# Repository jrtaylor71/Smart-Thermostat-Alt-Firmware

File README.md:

# Smart Thermostat Alt Firmware

A comprehensive, feature-rich smart thermostat system built on the ESP32 platform with professional PCB design. Perfect for DIY smart home automation with full Home Assistant integration.

## 🏗️ Hardware Credits

This project is **alternative firmware** for the excellent smart-thermostat hardware designed by **Stefan Meisner**.

**Original Hardware Project**: https://github.com/smeisner/smart-thermostat

We use Stefan's hardware design and provide an enhanced firmware implementation with advanced features including multi-core architecture, centralized display management, and comprehensive Home Assistant integration.

## 🌟 Key Features

- **📱 Local Touch Control**: ILI9341 TFT LCD with intuitive touch interface
- **🏠 Smart Home Ready**: Full MQTT integration with Home Assistant auto-discovery
- **🔄 Bidirectional Schedule Sync (v1.4.001)**: 7-day schedules stay in sync between thermostat and Home Assistant (device ↔ HA) with day/night periods and editable Heat/Cool/Auto temperatures
- **📅 7-Day Scheduling**: Comprehensive inline scheduling with day/night periods and editable Heat/Cool/Auto temperatures
- **🌡️ Dual Sensors**: AHT20 for ambient conditions + DS18B20 for hydronic systems
- **⚡ Multi-Stage HVAC**: Support for 2-stage heating and cooling systems
- **💨 Advanced Fan Control**: Auto, continuous, and scheduled cycling modes
- **🌤️ Weather Integration**: OpenWeatherMap and Home Assistant weather with color-coded icons on display
- **🌐 Modern Web Interface**: Complete tabbed interface with embedded scheduling - no separate pages
- **📡 Offline Operation**: Full functionality without WiFi connection
- **🔧 Professional PCB**: Custom PCB design for clean, permanent installation
- **🔄 OTA Updates**: Over-the-air firmware updates with real-time progress tracking
- **🔒 Factory Reset**: Built-in reset capability via boot button

## 🚀 Quick Start

### Hardware Requirements
- ESP32-S3-WROOM-1-N16 (16MB Flash, No PSRAM) 
- ILI9341 320x240 TFT LCD with XPT2046 Touch Controller
- AHT20 Temperature/Humidity Sensor (I2C)
- DS18B20 Temperature Sensor (optional, for hydronic heating)
- LD2410 24GHz mmWave Motion Sensor (optional, for display wake)
- 5x Relay Module for HVAC control
- Custom PCB by Stefan Meisner (files included)

### Software Setup
1. Install [PlatformIO](https://platformio.org/) IDE
2. Clone this repository
3. Open project in PlatformIO
4. Configuration optimized for ESP32-S3-WROOM-1-N16 (16MB flash)
5. Memory usage: RAM 15.2% (49728/327680 bytes); Flash 18.5% (1209901/6553600 bytes, default_16mb.csv partition)
6. Erase flash if you are using firmware from Stefan Meisner (original firmware).
7. Build and upload to ESP32-S3
8. Use touch interface to configure WiFi and settings

## 💻 Web Interface

Access the thermostat's web interface by navigating to its IP address:

### Tabbed Interface with Embedded Features

**Status Tab**: Real-time monitoring of:
- Current temperature and humidity
- Thermostat and fan modes
- Relay states and system status

**Settings Tab**: Complete configuration interface for:

- Temperature setpoints and control modes
- MQTT/Home Assistant integration
- WiFi network settings
- Multi-stage HVAC parameters
- Hydronic heating controls
- Fan scheduling options

**Schedule Tab**: Comprehensive 7-day scheduling:
- Day and night periods for each day of the week
- Editable Heat, Cool, and Auto temperatures for each period
- Time controls for period transitions
- Schedule enable/disable and override controls
- All options always visible - no hidden menus

**System Tab**: Device information and firmware updates

## 🏠 Home Assistant Integration

Automatic discovery and integration with Home Assistant:

1. Enable MQTT in thermostat settings
2. Configure MQTT broker details
3. Thermostat appears automatically in Home Assistant
4. Full control via Home Assistant interface (climate entity, helpers, and switches)
5. Bidirectional schedule sync: HA helpers (77 per thermostat) mirror the device schedule; edits on either side stay in sync
6. Supports climate entity with heating/cooling modes

## 🛠️ Advanced Features

### Multi-Stage Operation
- Intelligent staging based on time and temperature
- Configurable stage 2 activation parameters
- Prevents system short-cycling
- Optimizes energy efficiency

### Hydronic Heating Support
- DS18B20 water temperature monitoring
- Safety interlocks prevent operation when water is too cold
- Configurable high/low temperature thresholds
- Perfect for radiant floor heating systems

### Fan Control Options
- **Auto**: Fan runs only with heating/cooling
- **On**: Continuous fan operation
- **Cycle**: Scheduled fan operation (configurable minutes per hour)

### Motion Detection
- **LD2410 24GHz mmWave Sensor**: Automatic display wake on motion detection
- **Hardware Pins**: RX=15, TX=16, Motion=18
- **Robust Detection**: Works with sensors that don't respond to UART commands
- **Home Assistant Integration**: Motion sensor auto-discovery and status publishing
- **Energy Saving**: Display automatically sleeps when no motion detected
- **Seamless Operation**: Works alongside existing touch controls

### Safety Features
- Watchdog timer prevents system lockups
- Factory reset via boot button (10+ seconds)
- Temperature limit enforcement
- Graceful offline operation

## 🔧 Factory Reset

Press and hold the boot button for more than 10 seconds while the thermostat is running to restore all settings to defaults.

## 📄 License

This project is released under the GNU General Public License v3.0. Free to use, modify, and distribute.

## 🤝 Contributing

Contributions welcome! Please:
1. Fork the repository
2. Create a feature branch
3. Make your changes
4. Submit a pull request

## 📞 Support

- **Issues**: Use GitHub Issues for bug reports
- **Discussions**: GitHub Discussions for questions
- **Documentation**: Comprehensive docs included
- **Serial Debug**: Detailed logging at 115200 baud

## ⭐ Version

**Current Version**: 1.4.001 (January 2026)
### Release Notes: 1.4.001
- Bidirectional MQTT schedule synchronization (thermostat ↔ Home Assistant)
- Fixed day index off-by-one bug (MQTT Monday=0, firmware Sunday=0)
- Multi-thermostat support with centralized inbound automation and 77 outbound automations per device
- 77 Home Assistant helpers per thermostat (14 times, 42 temps, 21 booleans)
- Added automation generator and schedule templates for HA
- Updated documentation and quick-start guidance for schedule sync

### Previous Highlights (1.3.8)
- Weather Integration: Dual-source weather support (OpenWeatherMap and Home Assistant)
- Weather Display: Color-coded standard OWM icons with temperature, conditions, and high/low display
- Weather Web Interface: Dedicated weather tab with AJAX form submission
- Anti-Flicker Display: Cached redraw optimization for time and weather elements
- Enhanced Time Display: Improved format "HH:MM Weekday Mon D YYYY" with flicker elimination
- Weather Settings: Configurable update intervals (5-60 minutes) with state field for US cities
- Enhanced OTA Updates: Real-time progress tracking for upload and flash write operations
- Improved OTA UX: Integrated OTA interface in System tab with status messages and reboot timing
- 7-Day Scheduling System: Complete inline scheduling with day/night periods and editable Heat/Cool/Auto temperatures
- LD2410 Motion Sensor Integration: 24GHz mmWave radar for automatic display wake with robust detection
- Modern Tabbed Web Interface: All features embedded in main page - Status, Settings, Schedule, Weather, and System tabs
- Enhanced MQTT Integration: Motion sensor auto-discovery and status publishing to Home Assistant
- ESP32-S3-WROOM-1-N16 platform with 16MB flash optimization
- Modern Material Design color scheme with enhanced readability
- Complete thermostat functionality with Option C display system
- Enhanced MQTT/Home Assistant integration with temperature precision
- Professional PCB design (hardware by Stefan Meisner)
- Multi-stage HVAC support with intelligent staging
- Dual-core FreeRTOS architecture for ESP32-S3

## 🙏 Credits & Acknowledgments

**Hardware Design**: Stefan Meisner - [smart-thermostat](https://github.com/smeisner/smart-thermostat)  
**Alternative Firmware**: Jonn Taylor - Enhanced firmware implementation

This project demonstrates the power of open-source collaboration - combining excellent hardware design with advanced firmware capabilities.

---

**Created for the DIY smart home community**

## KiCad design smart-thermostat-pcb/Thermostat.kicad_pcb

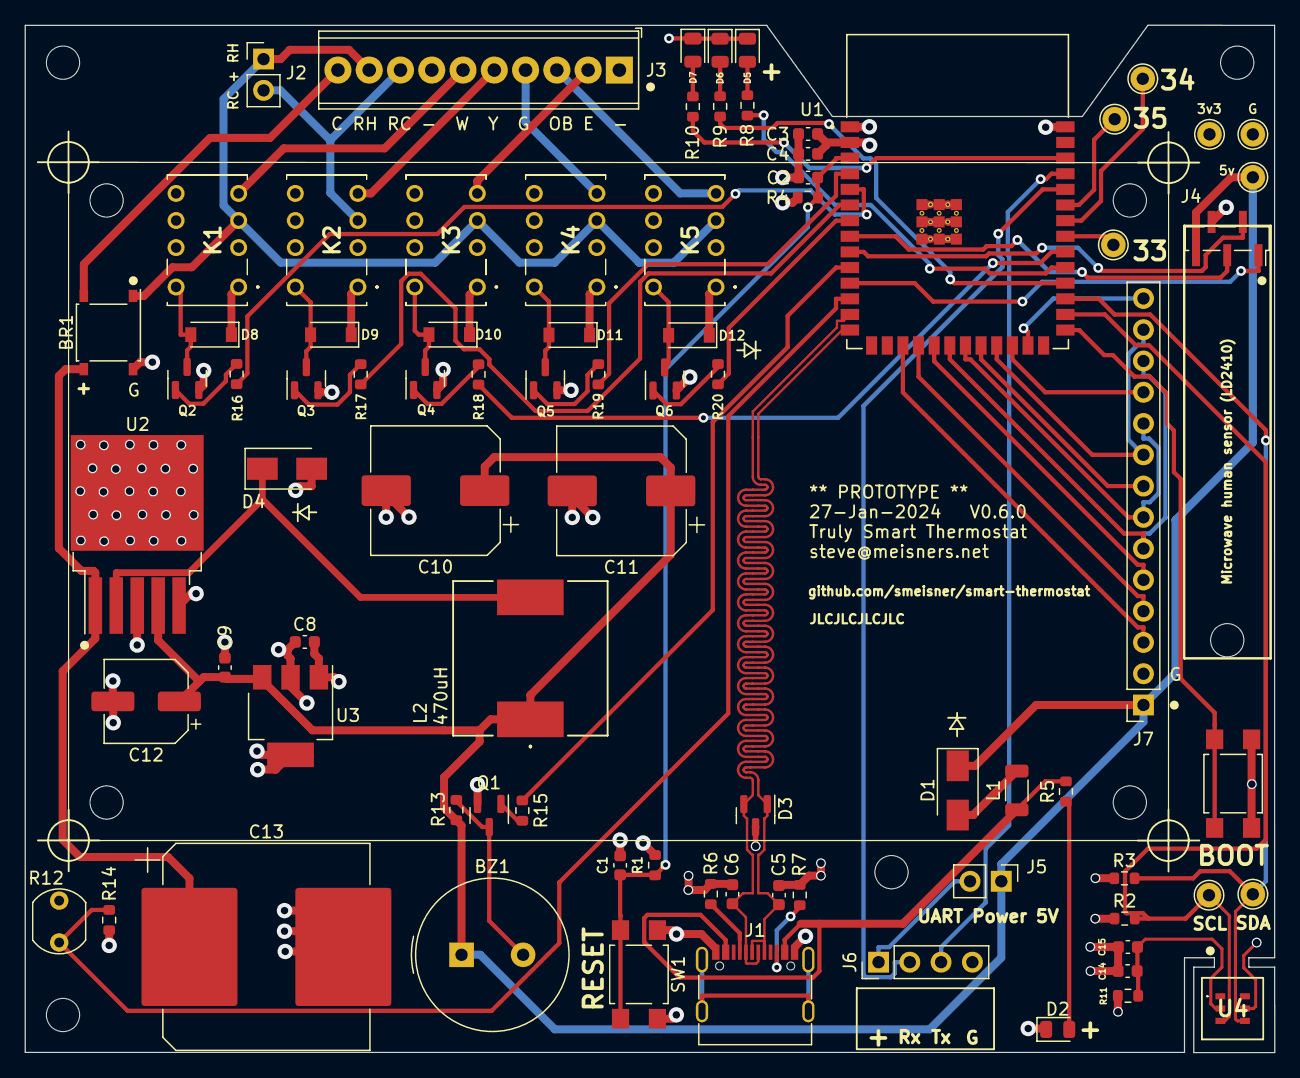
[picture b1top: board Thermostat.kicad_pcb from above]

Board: 4 copper layers, 101.5 x 83.4 mm, 91 parts (0 on the bottom side), 65 nets.

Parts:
BR1: MB6S; Diode_Bridge_Diotec_ABS
BZ1: Buzzer; Buzzer_TDK_PS1240P02BT_D12.2mm_H6.5mm
C1, C2: 1uF; C_0603_1608Metric
C3, C14: 0.1uF; C_0603_1608Metric
C4: 22uF; C_0603_1608Metric
C5, C6: 22pF; C_0603_1608Metric
C8, C9, C15: 10uF; C_0603_1608Metric
C10, C11: 470uF; CP_Elec_10x10
C12: 47uF; CP_Elec_6.3x7.7
C13: 680uF; CP_Elec_16x17.5
D1: D_Zener; D_SMA
D2, D5, D6, D7: LED; LED_0805_2012Metric
D3: SP0502BAHT; SOT-23
D4: SS34; D_SMA
D8, D9, D10, D11, D12: 1N4148W; D_SOD-123
H1, H2, H3, H4, H5, H6, H7, H8, H9: MountingHole; MountingHole_2.7mm_M2.5
J1: USB_C_Receptacle_USB2.0; USB_C_Receptacle_G-Switch_GT-USB-7010ASV
J2: RC+RH; PinHeader_1x02_P2.54mm_Vertical
J3: Screw_Terminal_01x10; TerminalBlock_Phoenix_MPT-0,5-10-2.54_1x10_P2.54mm_Horizont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
J4: LD2410; PinSocket_1x05_P1.27mm_Vertical_SMD_Pin1Right
J5: UART PWR; PinHeader_1x02_P2.54mm_Vertical
J6: Conn_01x04; PinHeader_1x04_P2.54mm_Vertical
J7: MSP3218; PinSocket_1x14_P2.54mm_Vertical
K1, K2, K3, K4, K5: UC2-3NJ; UC23NJ
L1: 600ohm; L_1206_3216Metric
L2: 470uH; IND_CDRH127_LDNP-470MC_SUM
Q1, Q2, Q3, Q4, Q5, Q6: 2N7002; SOT-23
R1, R2, R3, R4, R13, R14: 10k; R_0603_1608Metric
R5: 10K; R_0603_1608Metric
R6, R7: 5.1K; R_0603_1608Metric
R8, R10: 1K; R_0603_1608Metric
R9: 2K; R_0603_1608Metric
R11: 220; R_0603_1608Metric
R12: LDR07; R_LDR_5.1x4.3mm_P3.4mm_Vertical
R15: 1k; R_0603_1608Metric
R16, R17, R18, R19, R20: 470; R_0603_1608Metric
SW1: Reset; SW_SPST_TL3305A
SW2: Boot; SW_SPST_TL3305A
TP1: SCL; TestPoint_THTPad_D2.0mm_Drill1.0mm
TP2: SDA; TestPoint_THTPad_D2.0mm_Drill1.0mm
TP3: 3v3; TestPoint_THTPad_D2.0mm_Drill1.0mm
TP4, TP4#2, TP4#3, TP4#4: +5V; TestPoint_THTPad_D2.0mm_Drill1.0mm
TP5: GND; TestPoint_THTPad_D2.0mm_Drill1.0mm
U1: ESP32-S3-WROOM-1-N16; XCVR_ESP32-S3-WROOM-1-N16R2
U2: LM2596T-5; TO-263-5_TabPin3
U3: AMS1117-3.3; SOT-223-3_TabPin2
U4: AHT20

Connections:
+3V3: C3.1, C4.1, C8.1, D8.1 (K), D9.1 (K), D10.1 (K), D11.1 (K), D12.1 (K), K1.1 (COIL+), K2.1 (COIL+), K3.1 (COIL+), K4.1 (COIL+), K5.1 (COIL+), R1.2, R2.1, R3.1, R4.2, R11.2, R12.1, TP3.1, U1.2 (3V3), U3.2 (VO)
+5V: BZ1.1 (-), C9.1, C10.1, C11.1, C12.1, D1.1 (K), J4.5, J5.1, J7.1, L2.1, R13.2, TP4#3.1, U2.4 (FB), U3.3 (VI)
BUZZER: R15.1, U1.10 (IO17)
C: BR1.2, J3.10
E: J3.2, K3.4 (NO_1)
EN: C1.1, C2.1, R1.1, R4.1, SW1.2, U1.3 (EN)
G: J3.4, K4.4 (NO_1)
GND: BR1.4 (-), C1.2, C2.2, C3.2, C4.2, C5.2, C6.2, C8.2, C9.2, C10.2, C11.2, C12.2, C13.2, C14.2, C15.2, D2.1 (K), D3.3 (A), D4.2 (A), D5.1 (K), D6.1 (K), D7.1 (K), J1.A1 (GND), J1.A12 (GND), J1.B1 (GND), J1.B12 (GND), J4.4, J6.4, J7.2, Q1.2 (S), Q2.2 (S), Q3.2 (S), Q4.2 (S), Q5.2 (S), Q6.2 (S), R6.2, R7.2, R14.1, SW1.1, SW2.1, TP5.1, U1.1 (GND), U1.40 (GND), U1.41_1 (GND), U1.41_2 (GND), U1.41_3 (GND), U1.41_4 (GND), U1.41_5 (GND), U1.41_6 (GND), U1.41_7 (GND), U1.41_8 (GND), U1.41_9 (GND), U1.41_10 (GND), U1.41_11 (GND), U1.41_12 (GND), U1.41_13 (GND), U1.41_14 (GND), U1.41_15 (GND), U1.41_16 (GND), U1.41_17 (GND), U1.41_18 (GND), U1.41_19 (GND), U1.41_20 (GND), U1.41_21 (GND), U2.3 (GND), U2.5 (~ON/OFF), U3.1 (GND), U4.5 (GND)
HVAC_2STAGE: R18.2, U1.32 (IO39)
HVAC_COOL: R17.2, U1.6 (IO6)
HVAC_FAN: R19.2, U1.4 (IO4)
HVAC_HEAT: R16.2, U1.5 (IO5)
HVAC_RVALV: R20.2, U1.7 (IO7)
LD_RX: J4.3, U1.8 (IO15)
LD_TX: J4.2, U1.9 (IO16)
LED_COOL: R10.2, U1.38 (IO2)
LED_FAN: R9.2, U1.30 (IO37)
LED_HEAT: R8.2, U1.31 (IO38)
LIGHT_SENS: R12.2, R14.2, U1.12 (IO8)
MOTION: J4.1, U1.11 (IO18)
unnamed: BR1.3 (+), C13.1, U2.1 (VIN)
unnamed: BZ1.2 (+), Q1.3 (D), R13.1
unnamed: D1.2 (A), L1.2
unnamed: D2.2 (A), R5.2
unnamed: D4.1 (K), L2.2, U2.2 (OUT)
unnamed: D5.2 (A), R8.1
unnamed: D6.2 (A), R9.1
unnamed: D7.2 (A), R10.1
unnamed: D8.2 (A), K1.8 (COIL-), Q2.3 (D)
unnamed: D9.2 (A), K2.8 (COIL-), Q3.3 (D)
unnamed: D10.2 (A), K3.8 (COIL-), Q4.3 (D)
unnamed: D11.2 (A), K4.8 (COIL-), Q5.3 (D)
unnamed: D12.2 (A), K5.8 (COIL-), Q6.3 (D)
unnamed: J1.A5 (CC1), R6.1
unnamed: J1.B5 (CC2), R7.1
unnamed: J1.A4 (VBUS), J1.A9 (VBUS), J1.B4 (VBUS), J1.B9 (VBUS), L1.1, R5.1
unnamed: Q1.1 (G), R15.2
unnamed: Q2.1 (G), R16.1
unnamed: Q3.1 (G), R17.1
unnamed: Q4.1 (G), R18.1
unnamed: Q5.1 (G), R19.1
unnamed: Q6.1 (G), R20.1
unnamed: SW2.2, U1.27 (IO0)
unnamed: C14.1, C15.1, R11.1, U4.2 (VDD)
O/B: J3.3, K5.4 (NO_1)
RC: J2.2, J3.8, K2.3 (COM_1)
RH: BR1.1, J2.1, J3.9, K1.3 (COM_1), K3.3 (COM_1), K4.3 (COM_1), K5.3 (COM_1)
RXD0: J6.2, U1.36 (RXD0)
SCL: R2.2, TP1.1, U1.28 (IO35), U4.3 (SCL)
SDA: R3.2, TP2.1, U1.29 (IO36), U4.4 (SDA)
TFT_CLK: J7.7, J7.10, U1.21 (IO13)
TFT_CS: J7.3, U1.17 (IO9)
TFT_DC: J7.5, U1.19 (IO11)
TFT_LED: J7.8, U1.22 (IO14)
TFT_MISO: J7.9, J7.13, U1.23 (IO21)
TFT_MOSI: J7.6, J7.12, U1.20 (IO12)
TFT_RESET: J7.4, U1.18 (IO10)
TOUCH_CS: J7.11, U1.24 (IO47)
TOUCH_IRQ: J7.14, U1.25 (IO48)
TXD0: J6.3, U1.37 (TXD0)
UART_VCC: J5.2, J6.1
USB_D+: C5.1, D3.1 (K), J1.A6 (D+), J1.B6 (D+), U1.14 (IO20)
USB_D-: C6.1, D3.2 (K), J1.A7 (D-), J1.B7 (D-), U1.13 (IO19)
W: J3.6, K1.4 (NO_1)
Y: J3.5, K2.4 (NO_1)

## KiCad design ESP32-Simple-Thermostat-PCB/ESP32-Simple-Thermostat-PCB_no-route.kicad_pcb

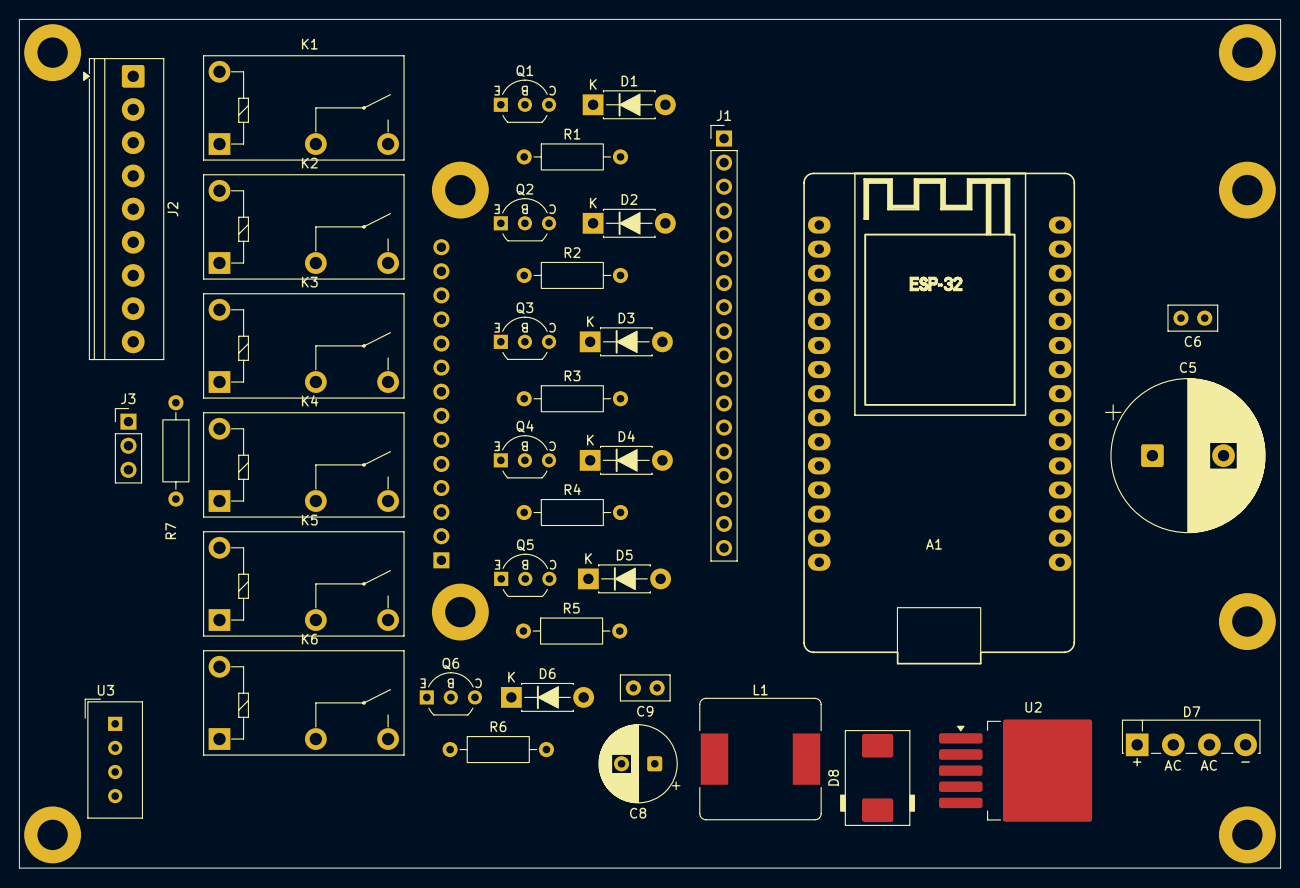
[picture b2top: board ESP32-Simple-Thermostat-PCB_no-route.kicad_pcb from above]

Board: 2 copper layers, 133.0 x 89.5 mm, 47 parts (1 on the bottom side), 39 nets, no tracks yet.

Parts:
A1: ESP32_DevKit_V1_DOIT_30GPIOs; DOIT_ESP32_DEVKIT_30Pins
C5: 1000uF_50V; CP_Radial_D16.0mm_P7.50mm
C6, C9: 100nF_Ceramic; C_Disc_D5.0mm_W2.5mm_P2.50mm
C8: 470uF_10V; CP_Radial_D8.0mm_P3.50mm
D1, D2, D3, D4, D5, D6: 1N4007; D_DO-41_SOD81_P7.62mm_Horizontal
D7: KBP210G; Diode_Bridge_KBP
D8: SS34; D_SMC
H1, H2, H3, H4, H5, H6, H7, H8: MountingHole_M3_3.2mm_Pad; MountingHole_3.2mm_Pad
J1: PINHD_1x18_Male; PinHeader_1x18_P2.54mm_Vertical
J2: Screw_Terminal_9_P3.50mm; TerminalBlock_Phoenix_PT-1,5-9-3.5-H_1x09_P3.50mm_Horizontal
J3: DS18B20; PinHeader_1x03_P2.54mm_Vertical
J4: 3.2 lcd tft; PinSocket_1x14_P2.54mm_Vertical
K1, K2, K3, K4, K5, K6: G5Q-1A; Relay_SPST_Omron-G5Q-1A
L1: 12uH_5.2A_1260; L_Bourns_SRR1260
Q1, Q2, Q3, Q4, Q5, Q6: 2N2222A-TO92; TO-92_Inline_Wide_EBC
R1, R2, R3, R4, R5, R7: 4.7k; R_Axial_DIN0207_L6.3mm_D2.5mm_P10.16mm_Horizontal
R6: Resistor; R_Axial_DIN0207_L6.3mm_D2.5mm_P10.16mm_Horizontal
U2: LM2596S-5; TO-263-5_TabPin3
U3: DHT11; Aosong_DHT11_5.5x12.0_P2.54mm

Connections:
3.3V: A1.1 (3.3V), J3.2, R7.2
+5V: A1.30 (VIN), C8.1, C9.1, D1.1 (K), D2.1 (K), D3.1 (K), D4.1 (K), D5.1 (K), D6.1 (K), J1.2, J1.5, J1.8, J1.11, J1.14, J1.17, J4.1, J4.8, K1.5, K2.5, K3.5, K4.5, K5.5, K6.5, L1.1, U2.4 (FB), U3.1 (VDD)
CS_15: A1.3 (D15/ADC2_CH3), J4.3
D12: A1.27 (ADC2_CH5/D12), J1.10, R4.2
D13: A1.28 (ADC2_CH4/D13), J1.4, R2.2
D14: A1.26 (ADC2_CH6/D14), J1.7, R3.2
D25: A1.23 (DAC1/ADC2_CH8/D25), J1.1, R1.2
D26: A1.24 (DAC2/ADC2_CH9/D26), J1.13, R5.2
D27: A1.25 (ADC2_CH7/D27), J1.16, J3.1, R7.1
D32: A1.22 (ADC1_CH4/D32), R6.2
DHT11_22: A1.14 (D22/SCL), U3.2 (DATA)
EN: A1.16 (EN), J4.4
G: J2.1, K1.3
GND: A1.2 (GND), A1.29 (GND), C5.2, C6.1, C8.2, C9.2, D7.4 (-), D8.2 (A), J1.3, J1.9, J1.12, J1.15, J1.18, J3.3, J4.2, Q1.1 (E), Q2.1 (E), Q3.1 (E), Q4.1 (E), Q5.1 (E), Q6.1 (E), U2.3 (GND), U2.5 (~ON/OFF), U3.4 (GND)
MISO_19: A1.10 (D19), J4.9, J4.13
MOSI_23: A1.15 (D23), J4.6, J4.12
unnamed: D1.2 (A), K1.1, Q1.3 (C)
unnamed: D2.2 (A), K2.1, Q2.3 (C)
unnamed: D3.2 (A), K3.1, Q3.3 (C)
unnamed: D4.2 (A), K4.1, Q4.3 (C)
unnamed: D5.2 (A), K5.1, Q5.3 (C)
unnamed: D6.2 (A), K6.1, Q6.3 (C)
unnamed: C5.1, C6.2, D7.1 (+), U2.1 (VIN)
unnamed: D8.1 (K), L1.2, U2.2 (OUT)
unnamed: Q1.2 (B), R1.1
unnamed: Q2.2 (B), R2.1
unnamed: Q3.2 (B), R3.1
unnamed: Q4.2 (B), R4.1
unnamed: Q5.2 (B), R5.1
unnamed: Q6.2 (B), R6.1
PUMP: J2.6, K6.3
SCK_18: A1.9 (D18), J4.7, J4.10
T_CS_4: A1.5 (D4/ADC2_CH0), J4.11
VAC-C: D7.3 (2), J2.8, K1.2, K2.2, K3.2, K4.2, K5.2, K6.2
VAC-R: D7.2 (1), J2.9
W: J2.2, K2.3
W2: J2.4, K4.3
Y: J2.3, K3.3
Y2: J2.5, K5.3

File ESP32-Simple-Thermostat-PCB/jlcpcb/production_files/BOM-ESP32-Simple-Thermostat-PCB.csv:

Comment,Designator,Footprint,LCSC,Quantity
MountingHole_M3_3.2mm_Pad,H3,MountingHole_3.2mm_Pad,,1
G5Q-1A,K1,Relay_SPST_Omron-G5Q-1A,,1
DHT11,U3,Aosong_DHT11_5.5x12.0_P2.54mm,,1
2N2222A-TO92,Q3,TO-92_Inline_Wide_EBC,,1
G5Q-1A,K6,Relay_SPST_Omron-G5Q-1A,,1
Screw_Terminal_9_P3.50mm,J2,"TerminalBlock_Phoenix_PT-1,5-9-3.5-H_1x09_P3.50mm_Horizontal",,1
MountingHole_M3_3.2mm_Pad,H7,MountingHole_3.2mm_Pad,,1
1N4007,D4,D_DO-41_SOD81_P7.62mm_Horizontal,,1
MountingHole_M3_3.2mm_Pad,H8,MountingHole_3.2mm_Pad,,1
External Relays,J1,PinHeader_1x18_P2.54mm_Vertical,,1
MountingHole_M3_3.2mm_Pad,H2,MountingHole_3.2mm_Pad,,1
100nF_Ceramic,C6,C_Disc_D5.0mm_W2.5mm_P2.50mm,,1
4.7k,R7,R_Axial_DIN0207_L6.3mm_D2.5mm_P10.16mm_Horizontal,,1
2N2222A-TO92,Q4,TO-92_Inline_Wide_EBC,,1
1N4007,D3,D_DO-41_SOD81_P7.62mm_Horizontal,,1
1N4007,D2,D_DO-41_SOD81_P7.62mm_Horizontal,,1
2N2222A-TO92,Q5,TO-92_Inline_Wide_EBC,,1
G5Q-1A,K5,Relay_SPST_Omron-G5Q-1A,,1
MountingHole_M3_3.2mm_Pad,H5,MountingHole_3.2mm_Pad,,1
4.7k,R1,R_Axial_DIN0207_L6.3mm_D2.5mm_P10.16mm_Horizontal,,1
ESP32_DevKit_V1_DOIT_30GPIOs,A1,DOIT_ESP32_DEVKIT_30Pins,,1
1N4007,D5,D_DO-41_SOD81_P7.62mm_Horizontal,,1
G5Q-1A,K2,Relay_SPST_Omron-G5Q-1A,,1
Resistor,R6,R_Axial_DIN0207_L6.3mm_D2.5mm_P10.16mm_Horizontal,,1
MountingHole_M3_3.2mm_Pad,H1,MountingHole_3.2mm_Pad,,1
4.7k,R5,R_Axial_DIN0207_L6.3mm_D2.5mm_P10.16mm_Horizontal,,1
4.7k,R3,R_Axial_DIN0207_L6.3mm_D2.5mm_P10.16mm_Horizontal,,1
470uF_10V,C8,CP_Radial_D8.0mm_P3.50mm,,1
KBP210G,D7,Diode_Bridge_KBP,,1
LM2596S-5,U2,TO-263-5_TabPin3,,1
2N2222A-TO92,Q1,TO-92_Inline_Wide_EBC,,1
1N4007,D1,D_DO-41_SOD81_P7.62mm_Horizontal,,1
2N2222A-TO92,Q6,TO-92_Inline_Wide_EBC,,1
DS18B20,J3,PinHeader_1x03_P2.54mm_Vertical,,1
1N4007,D6,D_DO-41_SOD81_P7.62mm_Horizontal,,1
4.7k,R2,R_Axial_DIN0207_L6.3mm_D2.5mm_P10.16mm_Horizontal,,1
MountingHole_M3_3.2mm_Pad,H6,MountingHole_3.2mm_Pad,,1
G5Q-1A,K4,Relay_SPST_Omron-G5Q-1A,,1
G5Q-1A,K3,Relay_SPST_Omron-G5Q-1A,,1
100nF_Ceramic,C9,C_Disc_D5.0mm_W2.5mm_P2.50mm,,1
2N2222A-TO92,Q2,TO-92_Inline_Wide_EBC,,1
SS34,D8,D_SMC,,1
MountingHole_M3_3.2mm_Pad,H4,MountingHole_3.2mm_Pad,,1
4.7k,R4,R_Axial_DIN0207_L6.3mm_D2.5mm_P10.16mm_Horizontal,,1
12uH_5.2A_1260,L1,L_Bourns_SRR1260,,1
1000uF_50V,C5,CP_Radial_D16.0mm_P7.50mm,,1
3.2 lcd tft,J4,PinSocket_1x14_P2.54mm_Vertical,,1

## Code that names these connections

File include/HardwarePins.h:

/*
 * HardwarePins.h - Hardware pin definitions for ESP32-S3 Thermostat
 * 
 * Central location for all GPIO pin assignments
 * ESP32-S3-WROOM-1 variant with 16MB flash
 */

#ifndef HARDWARE_PINS_H
#define HARDWARE_PINS_H

// ============================================================================
// BOOT AND RESET BUTTONS
// ============================================================================
#define BOOT_BUTTON 0  // GPIO0 - Boot button for factory reset (10 second hold)

// ============================================================================
// MOTION SENSOR (LD2410)
// ============================================================================
#define LD2410_RX_PIN 16   // UART2 RX (connect to LD2410 TX)
#define LD2410_TX_PIN 15   // UART2 TX (connect to LD2410 RX)
#define LD2410_MOTION_PIN 18  // Digital motion output pin (HIGH when motion detected)

// ============================================================================
// TEMPERATURE SENSORS
// ============================================================================
#define ONE_WIRE_BUS 41    // 1-Wire bus for DS18B20 hydronic temperature sensor

// ============================================================================
// DISPLAY (TFT_eSPI)
// ============================================================================
// SPI pins for TFT display (configured in TFT_Setup_ESP32_S3_Thermostat.h)
#define TFT_BACKLIGHT_PIN 14  // GPIO14 - PWM control for TFT backlight brightness

// ============================================================================
// LIGHT SENSOR
// ============================================================================
#define LIGHT_SENSOR_PIN 8    // ADC pin for photocell/light sensor

// ============================================================================
// RELAY CONTROL PINS (HVAC Outputs)
// ============================================================================
// Heat pump/heating relays
const int heatRelay1Pin = 5;    // GPIO5  - Heat Stage 1 (primary heating)
const int heatRelay2Pin = 7;    // GPIO7  - Heat Stage 2 (auxiliary/2nd stage heating)

// Cooling relays
const int coolRelay1Pin = 6;    // GPIO6  - Cool Stage 1 (primary cooling)
const int coolRelay2Pin = 39;   // GPIO39 - Cool Stage 2 (auxiliary/2nd stage cooling)

// Fan control
const int fanRelayPin = 4;      // GPIO4  - Fan relay (continuous fan operation)
// Pump control
const int pumpRelayPin = 40;    // GPIO40 - Pump relay (for hydronic heating systems)

// ============================================================================
// STATUS LED PINS (Visual Feedback)
// ============================================================================
const int ledFanPin = 37;       // GPIO37 - Fan status LED (green)
const int ledHeatPin = 38;      // GPIO38 - Heat status LED (red)
const int ledCoolPin = 2;       // GPIO2  - Cool status LED (blue)

// ============================================================================
// AUDIO OUTPUT
// ============================================================================
const int buzzerPin = 17;       // GPIO17 - Buzzer (5V through 2N7002 MOSFET)

// ============================================================================
// COMPATIBILITY MACROS (for unified codebase)
// ============================================================================
// Relay control pins - uppercase macro names for compatibility with main code
#define HEAT_RELAY_1_PIN heatRelay1Pin
#define HEAT_RELAY_2_PIN heatRelay2Pin
#define COOL_RELAY_1_PIN coolRelay1Pin
#define COOL_RELAY_2_PIN coolRelay2Pin
#define FAN_RELAY_PIN fanRelayPin
#define PUMP_RELAY_PIN pumpRelayPin

// Status LED pins - uppercase macro names
#define LED_FAN_PIN ledFanPin
#define LED_HEAT_PIN ledHeatPin
#define LED_COOL_PIN ledCoolPin

// Buzzer pin - uppercase macro name
#define BUZZER_PIN buzzerPin

// I2C pins for sensor communication (not used in Alt - only AHT20 which uses default I2C)
// These are defined for compatibility with copied main code
#define I2C_SDA_PIN 36  // Not physically connected in Alt hardware
#define I2C_SCL_PIN 35  // Not physically connected in Alt hardware

// OneWire pin for DS18B20 (maps to ONE_WIRE_BUS)
#define ONEWIRE_PIN ONE_WIRE_BUS

// ============================================================================
// PWM CONFIGURATION
// ============================================================================
// PWM channels for various outputs
const int PWM_CHANNEL = 0;            // Channel 0 - TFT backlight brightness
const int PWM_CHANNEL_HEAT = 1;       // Channel 1 - Heat LED brightness
const int PWM_CHANNEL_COOL = 2;       // Channel 2 - Cool LED brightness
const int PWM_CHANNEL_FAN = 3;        // Channel 3 - Fan LED brightness
const int PWM_CHANNEL_BUZZER = 4;     // Channel 4 - Buzzer PWM (tone generation)

// PWM frequency and resolution
const int PWM_FREQ = 5000;            // 5 kHz frequency
const int PWM_RESOLUTION = 8;         // 8-bit resolution (0-255)

// ============================================================================
// BRIGHTNESS CONTROL (Display Backlight)
// ============================================================================
const int MIN_BRIGHTNESS = 30;        // Minimum backlight brightness (0-255)
const int MAX_BRIGHTNESS = 255;       // Maximum backlight brightness (0-255)

// Light sensor thresholds for automatic brightness control
const int LIGHT_SENSOR_MIN = 100;     // Minimum useful light sensor reading
const int LIGHT_SENSOR_MAX = 3500;    // Maximum useful light sensor reading

// ============================================================================
// TIMING CONSTANTS
// ============================================================================
const unsigned long BRIGHTNESS_UPDATE_INTERVAL = 1000;  // Update brightness every 1 second
const unsigned long FACTORY_RESET_PRESS_TIME = 10000;   // 10 seconds for factory reset

// ============================================================================
// PROJECT NAMING AND BRANDING
// ============================================================================
#define PROJECT_NAME_SHORT "Smart Thermostat Alt Firmware"
#define UI_PRODUCT_LINE "Smart Thermostat Alt Firmware"
#define DEFAULT_HOSTNAME "Smart-Thermostat"
#define MQTT_MANUFACTURER "Tah Der"
#define MQTT_MODEL "Truly Smart Thermostat"

#endif // HARDWARE_PINS_H

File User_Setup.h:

// ESP32-S3 User Setup for TFT_eSPI library
// Pin assignments matching smart-thermostat hardware v0.04

#define ILI9341_DRIVER       // Define the display driver

#define TFT_MISO 21    // SPI MISO (smart-thermostat hardware)
#define TFT_MOSI 12    // SPI MOSI (smart-thermostat hardware)  
#define TFT_SCLK 13    // SPI Clock (smart-thermostat hardware)
#define TFT_CS   9     // Chip Select (smart-thermostat hardware)
#define TFT_DC   11    // Data/Command (smart-thermostat hardware)
#define TFT_RST  10    // Reset (smart-thermostat hardware)

#define TOUCH_CS 47    // Touch Chip Select (smart-thermostat hardware)

// Load glcd font
#define LOAD_GLCD   
#define LOAD_FONT2  
#define LOAD_FONT4  
#define LOAD_FONT6  
#define LOAD_FONT7  
#define LOAD_FONT8  
#define LOAD_GFXFF  

// Define the SPI frequency
#define SPI_FREQUENCY  20000000   // 20MHz for good performance
#define SPI_READ_FREQUENCY  20000000
#define SPI_TOUCH_FREQUENCY  2500000

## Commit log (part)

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2025-01-25 modified: src/Main-Thermostat.cpp
2025-01-25 new file: .pio/build/esp32dev/.sconsign310.dblite new file: .pio/build/esp32dev/FrameworkArduino/Esp.cpp.d new file: .pio/build/esp32dev/FrameworkArduino/Esp.cpp.o new file: .pio/build/esp32dev/Frame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
2025-01-25 modified: .pio/build/esp32dev/.sconsign310.dblite modified: .pio/build/esp32dev/FrameworkArduino/firmware_msc_fat.c.o modified: .pio/build/esp32dev/firmware.bin modified: .pio/build/esp32dev/firmware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
2025-01-29 modified: .pio/build/esp32dev/.sconsign310.dblite modified: .pio/build/esp32dev/FrameworkArduino/firmware_msc_fat.c.o modified: .pio/build/esp32dev/firmware.bin modified: .pio/build/esp32dev/firmware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
2025-04-16 Cleanup autochangeover
    Cleanup autochangeover
2025-04-19 modified: .pio/build/esp32dev/.sconsign310.dblite modified: .pio/build/esp32dev/FrameworkArduino/firmware_msc_fat.c.o modified: .pio/build/esp32dev/firmware.bin modified: .pio/build/esp32dev/firmware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
2025-04-29 modified: .pio/build/esp32dev/.sconsign310.dblite modified: .pio/build/esp32dev/firmware.bin modified: .pio/build/esp32dev/firmware.elf modified: .pio/build/esp32dev/firmware.map new file: .pio/build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
2025-05-01 new file: .pio/build/esp32dev/idedata.json modified: README.md
2025-05-01 new file: img/IMG_20250501_151129758.jpg
2025-05-01 new file: img/web-settings.png new file: img/web-status.png
2025-05-01 new file: .pio/build/esp32dev/idedata.json modified: README.md
2025-11-15 new file: .copilot deleted: .pio/build/esp32dev/.sconsign310.dblite deleted: .pio/build/esp32dev/FrameworkArduino/Esp.cpp.d deleted: .pio/build/esp32dev/FrameworkArduino/Esp.cpp.o deleted: .pio/build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
2025-11-18 modified: ESP32-Simple-Thermostat-PCB/ESP32-Simple-Thermostat-PCB.kicad_pcb new file: ESP32-Simple-Thermostat-PCB/ESP32-Simple-Thermostat-PCB_no-route-backups/ESP32-Simple-Thermostat-PCB_no-route-202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
2025-11-20 Version 1.0.5: Option C display system + temperature precision - FULLY TESTED
    ✅ CONFIRMED WORKING IN LIVE TESTING:
    - Option C centralized display update system operational
    - Real-time HVAC mode switching (heat→cool→off) working perfectly
    - Temperature precision fixed to 1 decimal place for Home Assistant
    - Mutex-protected multi-core architecture stable with no contention
    - Display indicators synchronized with relay state changes within 250ms
2025-11-20 Add proper hardware credits and acknowledgments
    - Updated file header to clarify this is alternative firmware
    - Added credits to Stefan Meisner for original smart-thermostat hardware design
    - Referenced original hardware project: https://github.com/smeisner/smart-thermostat
    - Added dedicated Credits & Acknowledgments section to README
    - Updated version to 1.0.5 to reflect current firmware capabilities
    - Emphasized this is enhanced firmware for existing hardware design
2025-11-20 Release v1.0.7: Material Design colors + ESP32-S3-WROOM-1-N16 optimization
    Hardware & Platform Updates:
    - Fix ESP32-S3-WROOM-1-N16 configuration with 16MB flash support
    - Update partition table from default.csv to huge_app.csv
    - Flash utilization improved: 72.8% → 30.3% (1.31MB → 3.14MB available)
    - Correct all pin definitions for ESP32-S3 platform
    Visual & UI Improvements:
2025-11-20 Project rename: ESP32-Simple-Thermostat → Smart Thermostat Alt Firmware
    Major Changes:
    - Updated all project references and branding throughout codebase
    - Changed default hostname from 'ESP32-Simple-Thermostat' to 'Smart-Thermostat-Alt'
    - Updated web interface title to 'Smart Thermostat Alt Firmware'
    - Refreshed all documentation files (README, DOCUMENTATION, DEVELOPMENT_GUIDE)
    - Updated source code headers and license references
2025-11-20 docs: Update project documentation to reflect ESP32-S3 architecture and v1.0.8 features
    - Updated DEVELOPMENT_GUIDE.md with ESP32-S3-WROOM-1-N16 specifications
    - Refreshed DOCUMENTATION.md with dual-core FreeRTOS architecture details
    - Restructured PROJECT_STRUCTURE.md to match current project organization
    - Updated README.md with current version 1.0.8 features and capabilities
    - Cleaned up legacy PCB design files from old project structure
    - Updated .copilot with current project context and development patterns
2025-11-20 feat: Add modern responsive web interface with Material Design
    - Create WebInterface.h with modern CSS framework and responsive design
    - Create WebPages.h with HTML template generators for all pages
    - Replace basic HTML web pages with professional Material Design interface
    - Add responsive grid layouts for mobile and desktop compatibility
    - Implement tabbed navigation for Status/Settings/System management
    - Add color-coded status indicators and temperature gauges
2025-11-21 Enhanced web interface with modern tabbed design and integrated OTA updates
    - Fixed HTML structure bug that was causing System tab to render blank
    - Reorganized web interface into clean 3-tab design: Status, Settings, System
    - Integrated OTA firmware update functionality directly into System tab
    - Added comprehensive system information display (IP, MAC, memory, uptime, etc.)
    - Improved CSS styling with Material Design elements and proper tab switching
    - Added confirmation dialogs for system actions (reboot, factory reset)
2025-11-21 deleted: Thermostat-sch.pdf new file: thermostat-pcb.pdf new file: thermostat-sch.pdf
2025-11-21 feat: v1.1.0 - Complete 7-Day Scheduling System with Inline Web Interface
    Major Features Added:
    • 7-Day Scheduling System with day/night periods for each day
    • Editable Heat, Cool, and Auto temperatures for each period
    • Inline tabbed web interface - no separate pages
    • Always-visible schedule options with no hidden menus
    • Per-day enable/disable and time controls
2025-11-21 Add LD2410 motion sensor integration v1.1.0
    - Implement 24GHz mmWave motion sensor for display wake functionality
    - Add robust detection logic for sensors that don't respond to UART commands
    - Integrate motion-based display wake with existing touch controls
    - Add MQTT auto-discovery for Home Assistant motion sensor entity
    - Include motion sensor status publishing with periodic updates
    - Update comprehensive documentation across all files
2025-11-23 modified: .pio/libdeps/esp32-s3-wroom-1-n16/integrity.dat modified: platformio.ini modified: src/Main-Thermostat.cpp
2025-11-25 Fix display indicators - use state flags instead of GPIO reads and update every 500ms from main loop
2025-11-25 Improve fan logic: state guards, fix cycle mode interruption, implement 5-minute increment scheduling
2025-11-25 Fix: Respect fanRelayNeeded in auto mode and activate functions
    - In auto mode, only control fan if fanRelayNeeded=true
    - When fanRelayNeeded=false, thermostat stays off and HVAC controls fan
    - Updated handleFanControl() and activate functions to check fanRelayNeeded
    - Fixes issue where fan would come on during heating/cooling even when not needed
2025-11-25 Add exponential moving average (EMA) filtering to AHT20 sensor readings for temperature and humidity smoothing
2025-11-30 v1.2.2 - Fixed motion wake with improved filtering and data freshness checks
2025-11-30 LD2410 safety: pre-drain UART to avoid MyLD2410::readFrame() overflow; fix I2C mutex ordering; bump MyLD2410 to v1.2.5
2025-11-30 Phase 1: Upgrade Adafruit Unified Sensor to v1.1.15 (patch update, low risk)
2025-11-30 Phase 1: Upgrade DallasTemperature to v4.0.5
2025-11-30 Auto-upgrade ESPAsyncWebServer to v1.2.4
2025-12-01 Remove redundant standalone /update page endpoint
    OTA functionality is now fully integrated into the System tab of the main interface. The standalone page was redundant and removed to reduce code duplication and improve maintainability.
    Changes:
    - Removed ~70 lines of HTML/CSS/JS from /update GET endpoint
    - Kept /update POST handler and /update_status endpoint for System tab integration
    - Reduced flash usage from 15.8% to 15.7%
2025-12-01 Update documentation to v1.3.0 with OTA improvements
    - Updated all documentation files to reflect current version 1.3.0
    - Added detailed OTA update improvements to feature lists
    - Documented real-time progress tracking for uploads and flash writes
    - Added development session notes for OTA enhancement work
    - Updated version history with v1.3.0 and v1.2.4 entries
    - Enhanced API endpoint documentation with OTA status endpoints
2025-12-01 Add build date and time to serial debug.
2025-12-01 v1.3.5 - Weather integration with OpenWeatherMap/HA, color-coded icons, improved time display
2025-12-01 docs: add new image KIMG20251201_111834902.JPG
2025-12-01 chore: track default_16mb.csv partition table
2025-12-24 Version 1.3.8: Centralize hardware pins in include/HardwarePins.h, remove duplicate definitions from Main-Thermostat.cpp, and verify compilation. Also minor cleanup in weather/web modules and platfor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
2025-12-24 removed old files
2025-12-28 Front case: trim standoff nearest display to avoid interference\n\n- Auto-detect closest standoff to display opening\n- Cut a small flat on facing side for clearance\n- Regenerate STEP/STL/FCStd outp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
2026-01-01 Fix MQTT temperature decimal precision and add firmware organization tools
    - Fix current temperature MQTT publish to use snprintf for consistent 1 decimal place formatting
    - Add build.sh wrapper script for automated firmware organization after builds
    - Add organize_firmware.sh to copy firmware files to timestamped directories
    - Add VS Code tasks for build + organize workflow
    - Create flash.sh script in each build directory for easy ELF flashing with esptool
2026-01-01 Add compiled firmware binaries
    - Add firmware/build_* directories with compiled bootloader, firmware, and partition binaries
    - Add latest_* symlinks for easy access to most recent build
    - Add flash.sh scripts for easy flashing with esptool
2026-01-01 v1.3.9: Add heat pump reversing valve support and multi-variant builds
    Features:
    - Heat pump reversing valve support (mutually exclusive with stage 2 heating)
    - Web interface checkbox with JavaScript mutual exclusion
    - Conditional relay control in heating/cooling activation
    - Dynamic status page display based on enabled features
    - Support for ESP32-S3 variants: 4MB, 8MB, 16MB, 32MB flash
2026-01-04 Cleanup firmware directory.
2026-01-14 Fix schedule.
2026-01-21 Add alignment pin holes to case assembly: back flange and front side walls
2026-01-24 Push firmware
2026-01-27 Cleanup old files.
2026-01-29 Add notches to sensor box to clear back case lip.
2026-02-22 Fix brightness not getting saved to NVM.
2026-02-22 v1.4.009: Touch calibration system, enhanced fan control, dual hydronic sensors
    Major Features:
    - Touch Screen Calibration System: On-device calibration via System Info page
    - Calibrate button: Interactive touch calibration with corner-tap routine
    - Clear Cal button: Reset calibration and reboot to defaults
    - Non-blocking startup with hardware-tested default values (426, 3526, 248, 3417, 7)
    - Debug logging for calibration values in boot log
2026-03-02 Fix displayed set temp when schedule is running.
2026-04-15 Release 1.4.015
    Include Wi-Fi startup/reconnect lockup fix
2026-05-02 fix statge 2 heating issue
2026-05-14 Release 1.5.003
2026-05-14 Release 1.5.004
